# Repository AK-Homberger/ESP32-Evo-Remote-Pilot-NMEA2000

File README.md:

# ESP32 Evolution Remote Pilot NMEA2000
This is a Remote Control for an Evolution EV-1 Auto Pilot via NMEA2000 (SeaTalk-NG).

It is based on the work of this project in GitHub: https://github.com/matztam/raymarine-evo-pilot-remote.
Many thanks for all the work to identify the NMEA 2000 codes for the EV-1 Course Computer.

The hardware consists of an ESP32 NodeMCU (here from AZ-Delivery), a CAN bus transceiver, a 433MHz receiver (RXB6) and a power converter.
Thats's all what is required to control an EV-1 based Auto Pilot with a simple 433 MHz remote control.

A standard 4 button 433 MHz KeyFob is used to send (+1 / -1 degree) and (+10 / -10 degrees) course changes to the autopilot (Auto/Standby is optional and requires two more buttons or an additional KeyFob). An accustical feedback for each received key is provided with a piezo buzzer tone. I tried to use the alarm function of the MFD (as within the Seatalk remote control). But so far I was not successful to send any alarm PGN that generates an alarm on the MFD.

For questions/discussions regarding the project you can use the OpenBoatProjects area this [Sailing Forum](https://www.segeln-forum.de/board194-boot-technik/board35-elektrik-und-elektronik/board195-open-boat-projects-org/77895-evo-autopilot-fernbedienung-mit-nmea2000/?s=b9460d50db9b29c916016f0e035fa62268823680). 

It's a German Sailing Forum, but other languages (preferred English) are welcome.

The schmatics file and the [pcb details](https://github.com/AK-Homberger/ESP32-Evo-Remote-Pilot-NMEA2000/blob/master/ESP32EvoPilotRemotePCB.pdf) are in the KiCAD folder.
You can simply order a board from aisler.net: https://aisler.net/p/SXWTZTTS

The code is using the NMEA 2000 libraries from Timo Lappalainen (https://github.com/ttlappalainen). 

Download and install the following libraries from GitHub link above:

 - NMEA2000
 - NMEA2000_esp32
 
The Remote Control is using the RCswitch library (to be installed with the Arduino IDE Library Manager).

For the ESP32 CAN bus, I use the "Waveshare SN65HVD230 Can Board" as transceiver. It works well with the ESP32 (GPIO pins 4 and 5). 
The 12 Volt is reduced to 5 Volt with a DC Step Down Converter (D24V10F5, https://www.pololu.com/product/2831).

GPIO 15 is used for the data from the RXB6 receiver. As antenna please use a short wire (e.g. 17,3 cm).
GPIO 2 is used to generate accustical feedback with a piezo buzzer.

# Programming the 433 MHz KeyFob

For programming the KeyFob please use the sketch ESP32_433_Programming.ino (https://github.com/AK-Homberger/ESP32-Evo-Remote-Pilot-NMEA2000/tree/master/ESP32_433_Programming). The Transmitter is connected to GPIO 19.

You should change the four codes in the software to individual random numbers. The same codes have to be copied to the programing sketch. 

Send each code individually and programm the keys of the remote according to the programming description of your KeyFob. Press "Send" button in serial console for next key. 

Key 1 = button A = -1 degree

Key 2 = button B =  +1 degree

Key 3 = button C = -10 degrees

Key 4 = button D = +10 degrees

If you use Auto/Standby function you also have to program the two additional buttons accordingly. After programming you can check directly if codes are programmed correctly. Just press the key on the remote and check if the shown value is correct.

It is possible to integrate the Remote Control code also in other ESP32 NMEA2000 projects (like the WiFi Gateway). But unfortunately the WLAN interfers with the 433 MHz receiver. Either RF part or interrupt for the RCSwitch). I noticed problems with the correct recognition of keys from the remote. As a result, I would suggest to avoid the integration in any other project with WLAN.

# Remove the 120 ohm resistor from the transceiver
For unknown reasons, many CAN bus transceivers for the ESP32 have a 120 Ohm resistor built into them. The resistor does not belong to the devices at the ends of the stub lines, but to the ends of the backbone cable.

Whether the transceiver contains a 120 ohm resistor can be determined either by looking at the [circuit diagram](https://github.com/AK-Homberger/NMEA2000-Workshop/blob/main/Docs/SN65HVD230%20CAN%20Board_SCH.pdf) or by measuring with the multimeter.

A knife tip is suitable for removing the SMD resistor. Use it to scratch or pry off the resistance. With the transceiver shown here, place the tip of the knife in front of the resistor (between the chip and the resistor) and support the knife against the chip. Then lever the tip against the resistance and use it to scratch / loosen / break the resistance. Whichever happens first.

It then looks like the picture. Then measure to be on the safe side. Without a 120 ohm resistor, the multimeter shows approx. 75 kOhm.

# Parts:

- Board (PCB) [Link](https://aisler.net/p/SXWTZTTS)
- ESP32 [Link](https://www.amazon.de/AZDelivery-NodeMCU-Development-Nachfolgermodell-ESP8266/dp/B071P98VTG/ref=sxts_sxwds-bia-wc-drs3_0?__mk_de_DE=%C3%85M%C3%85%C5%BD%C3%95%C3%91&cv_ct_cx=ESP32&dchild=1&keywords=ESP32) 
- RXB6 433 MHz receiver [Link](https://www.makershop.de/en/module/funk/rxb6-433mhz-antenne/)
- SN65HVD230 [Link](https://eckstein-shop.de/WaveshareSN65HVD230CANTransceiverBoard33V2CESDProtection)
- D24V10F5 [Link](https://eckstein-shop.de/Pololu5V2C1AStep-DownSpannungsreglerD24V10F5)
- Buzzer [Link](https://www.reichelt.de/de/en/developer-boards-active-piezo-buzzer-module-debo-piezo-p239111.html?&nbc=1)
- Resistor 3,3 KOhm [Link](https://www.reichelt.de/de/en/carbon-film-resistor-1-4-w-5-3-3-kohm-1-4w-3-3k-p1397.html?&nbc=1)
- Transistor BC547 [Link](https://www.reichelt.de/bipolartransistor-npn-45v-0-1a-0-5w-to-92-bc-547b-dio-p219082.html?search=BC547)
- Connector 2-pin [Link](https://www.reichelt.de/de/en/2-pin-terminal-strip-spacing-5-08-akl-101-02-p36605.html?&nbc=1)

For programming:
433MHz transmitter [Link](https://www.digikey.de/product-detail/de/sparkfun-electronics/WRL-10534/1568-1175-ND/5673761) or [Link2](https://www.makershop.de/en/module/funk/433-sender-empfaenger/). The second one has only internal antenna.

Remote Control (KeyFob):  [Link](https://www.amazon.de/XCSOURCE-Elektrische-Universal-Garagentor-Fernbedienung-Ersatz-Schl%C3%BCsselanh%C3%A4nger-HS641/dp/B01KJRGMHI/ref=sr_1_9?__mk_de_DE=%C3%85M%C3%85%C5%BD%C3%95%C3%91&dchild=1&keywords=433+mhz+fernbedienung&qid=1601302510&sr=8-9) or [Link2](https://www.amazon.de/EasyULT-Handsender-Fernbedienung-Automatische-Garagentor%C3%B6ffner/dp/B0829WXGR5/ref=sr_1_15?__mk_de_DE=%C3%85M%C3%85%C5%BD%C3%95%C3%91&dchild=1&keywords=433+mhz+fernbedienung&qid=1601307082&sr=8-15) or [Link3](https://de.aliexpress.com/item/4000850169472.html?spm=a2g0s.9042311.0.0.15244c4dubWD35)

# Updates
- Version 0.7, 29.08.2021: Switch off WiFi and BT completely.

- Version 0.6, 16.12.2020: Changed PCB layout to Rev 1.2. Corrected orientation of ESP32 (USB connector to outside).

- Version 0.5, 05.11.2020: Changed PCB layout to Rev 1.1. Bigger terminal block (5.08 mm) and different transitor footprint for easy soldering.

- Version 0.5, 30.10.2020: Added KiCAD files and PCB. 

- Version 0.5, 25.09.2020: Changed BeepOn() in code to generate beep even if no EV-1 device is found (to alow testing). 

- Version 0.4, 04.08.2020: Changed TX pin from 2 to 5. Addedd buzzer to pin 2. Store/restore last used NodeAddress.

- Version 0.2, 26.07.2020: Avoid using delay(), added SetN2kPGN65361 (Seatalk Alarm State) to allow alarm beep for key received feedback.

- Version 0.1, 24.07.2020: Initial version.

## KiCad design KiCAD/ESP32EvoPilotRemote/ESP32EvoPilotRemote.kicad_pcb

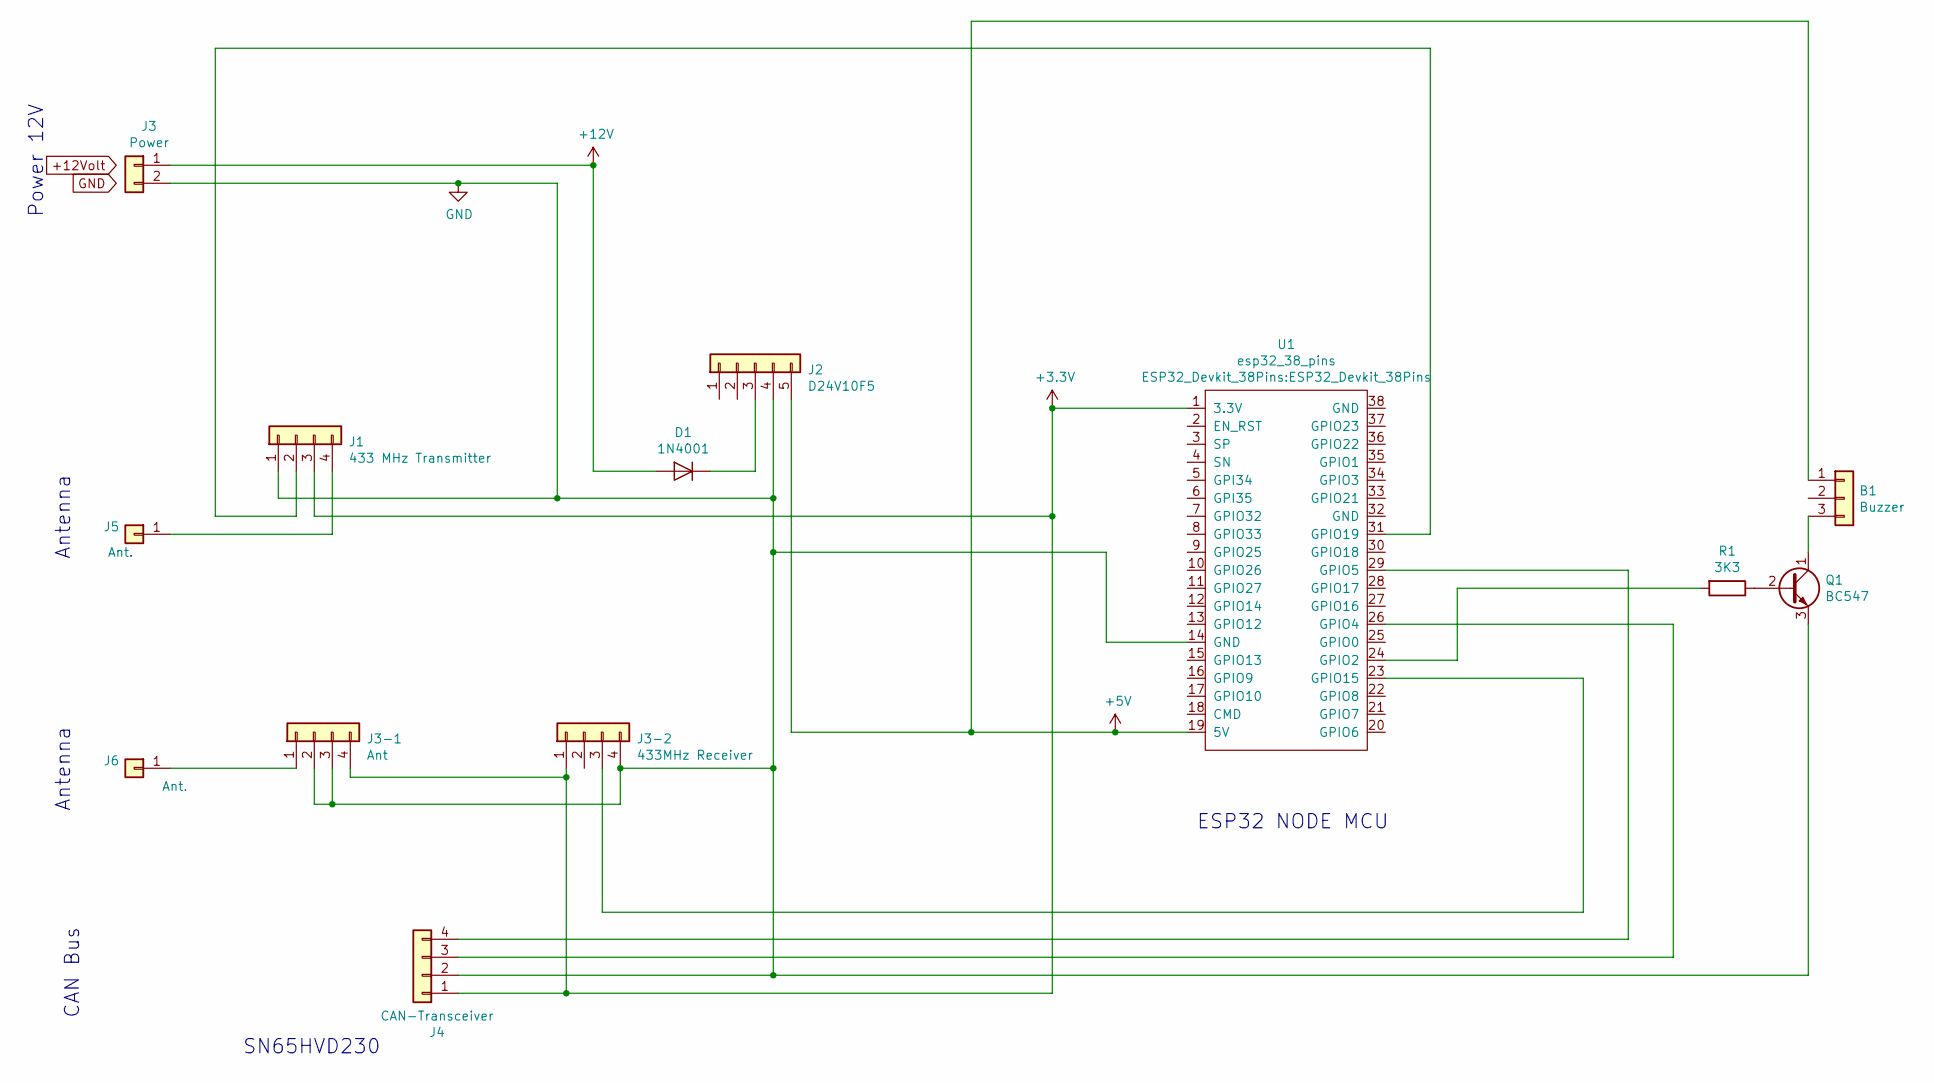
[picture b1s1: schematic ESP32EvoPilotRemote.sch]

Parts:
B1: Buzzer; PinHeader_1x03_P2.54mm_Vertical
D1: 1N4001; D_DO-41_SOD81_P10.16mm_Horizontal
J1: 433 MHz Transmitter; PinHeader_1x04_P2.54mm_Vertical
J2: D24V10F5; PinHeader_1x05_P2.54mm_Vertical
J3: Power; TerminalBlock_bornier-2_P5.08mm
J3-1: Ant; PinHeader_1x04_P2.54mm_Vertical
J3-2: 433MHz Receiver; PinHeader_1x04_P2.54mm_Vertical
J4: CAN-Transceiver; PinHeader_1x04_P2.54mm_Vertical
J5, J6: Ant.; Pin_D1.0mm_L10.0mm
Q1: BC547; TO-92_HandSolder
R1: 3K3; R_Axial_DIN0207_L6.3mm_D2.5mm_P10.16mm_Horizontal
U1: esp32_38_pins; ESP32_Devkit_38Pins

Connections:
+3V3: J1.3, J3-1.4, J3-2.1, J4.1, U1.1 (3.3V)
+5V: B1.1, J2.5, U1.19 (5V)
+12V: D1.2 (A), J3.1
GND: J1.1, J2.4, J3.2, J3-1.2, J3-1.3, J3-2.4, J4.2, Q1.3 (E), U1.14 (GND)
unnamed: B1.3, Q1.1 (C)
unnamed: D1.1 (K), J2.3
unnamed: J1.2, U1.31 (GPIO19)
unnamed: J1.4, J5.1
unnamed: J3-1.1, J6.1
unnamed: J3-2.3, U1.23 (GPIO15)
unnamed: J4.3, U1.26 (GPIO4)
unnamed: J4.4, U1.29 (GPIO5)
unnamed: Q1.2 (B), R1.1
unnamed: R1.2, U1.24 (GPIO2)

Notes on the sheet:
ESP32 NODE MCU
SN65HVD230
CAN Bus
Power 12V
Antenna

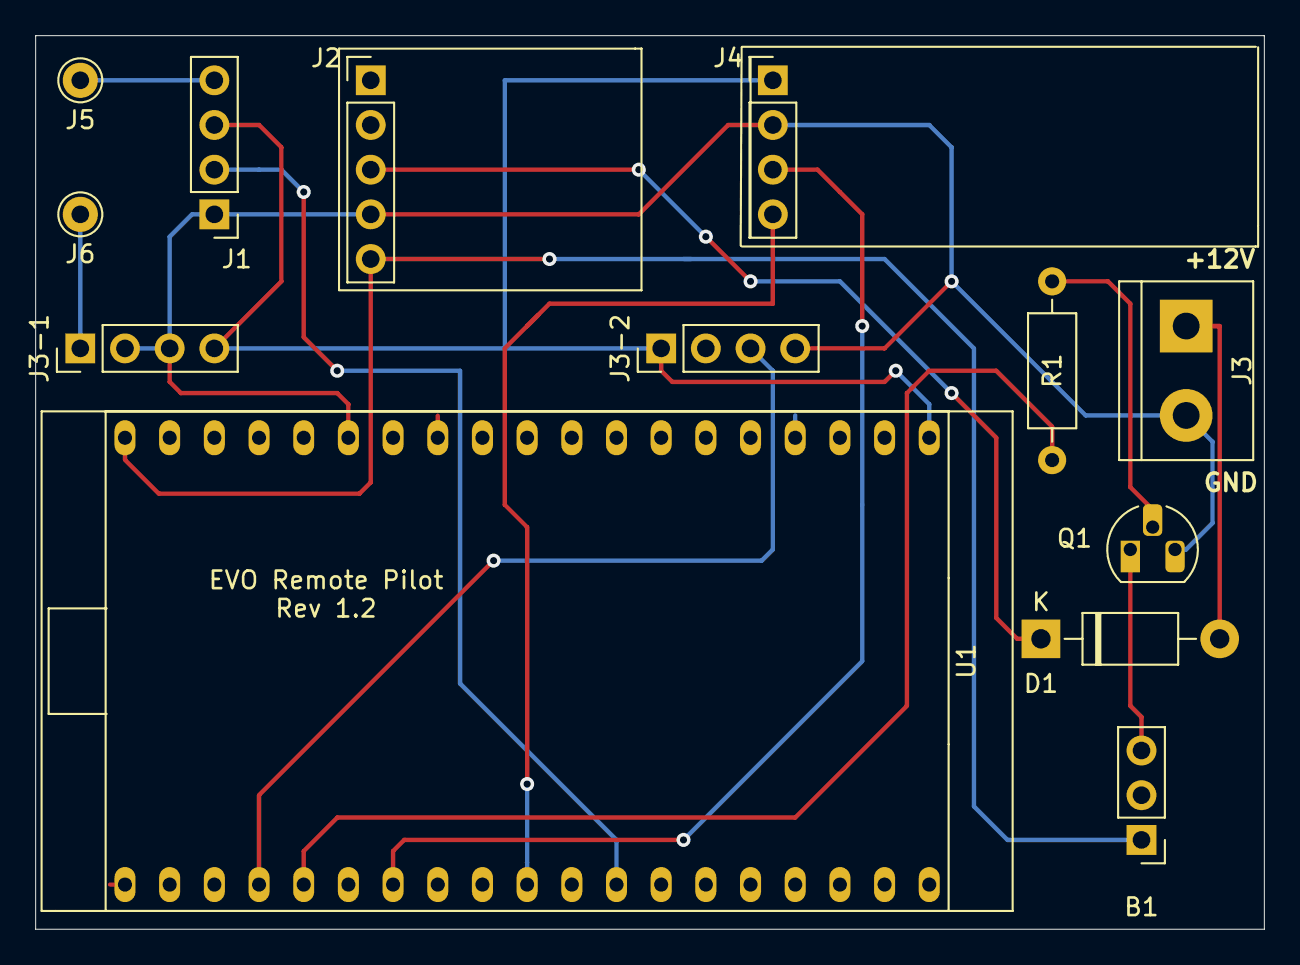
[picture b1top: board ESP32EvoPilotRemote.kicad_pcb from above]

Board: 2 copper layers, 69.8 x 50.8 mm, 13 parts (0 on the bottom side), 14 nets.

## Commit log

2020-07-24 Create LICENSE
2020-07-25 Added 433MHz transmitter.
2020-07-25 Added transmitter.
2020-07-26 Avoid delay() and added SetN2kPGN65361 (Seatalk Alarm State)
2020-08-04 Changed TX pin from 2 to 5. Added buzzer (pin 2).
2020-08-04 Changed TX pin from 2 to 5. Addedd buzzer (pin 2). Store/restore last NodeAddress.
2020-08-04 Changed TX pin from 2 to 5. Addedd buzzer (pin 2). Store/restore last…
2020-08-04 Changed TX pin from 2 to 5. Addedd buzzer (pin 2). Store/restore last NodeAddress.
2020-08-04 Changed TX pin from 2 to 5. Addedd buzzer (pin 2). Store/restore last Node Address.
2020-09-25 Changed BeepOn() in code to generate beep even if no EV-1 device is found (to allow testing).
2020-09-25 Changed BeepOn() in code to generate beep even if no EV-1 device is found (to alow testing).
2020-10-30 Added KiCAD files
2020-11-05 Version 1.1
2020-11-05 Version 1.1
    Bbigger terminal (5 mm) and other transistor footprint for easier soldering.
2020-12-16 Version 1.2
2021-08-29 Switch off WiFi and BT completely.
2022-02-05 Use new ESP32-API function name "esp_efuse_mac_get_default(chipid);"
